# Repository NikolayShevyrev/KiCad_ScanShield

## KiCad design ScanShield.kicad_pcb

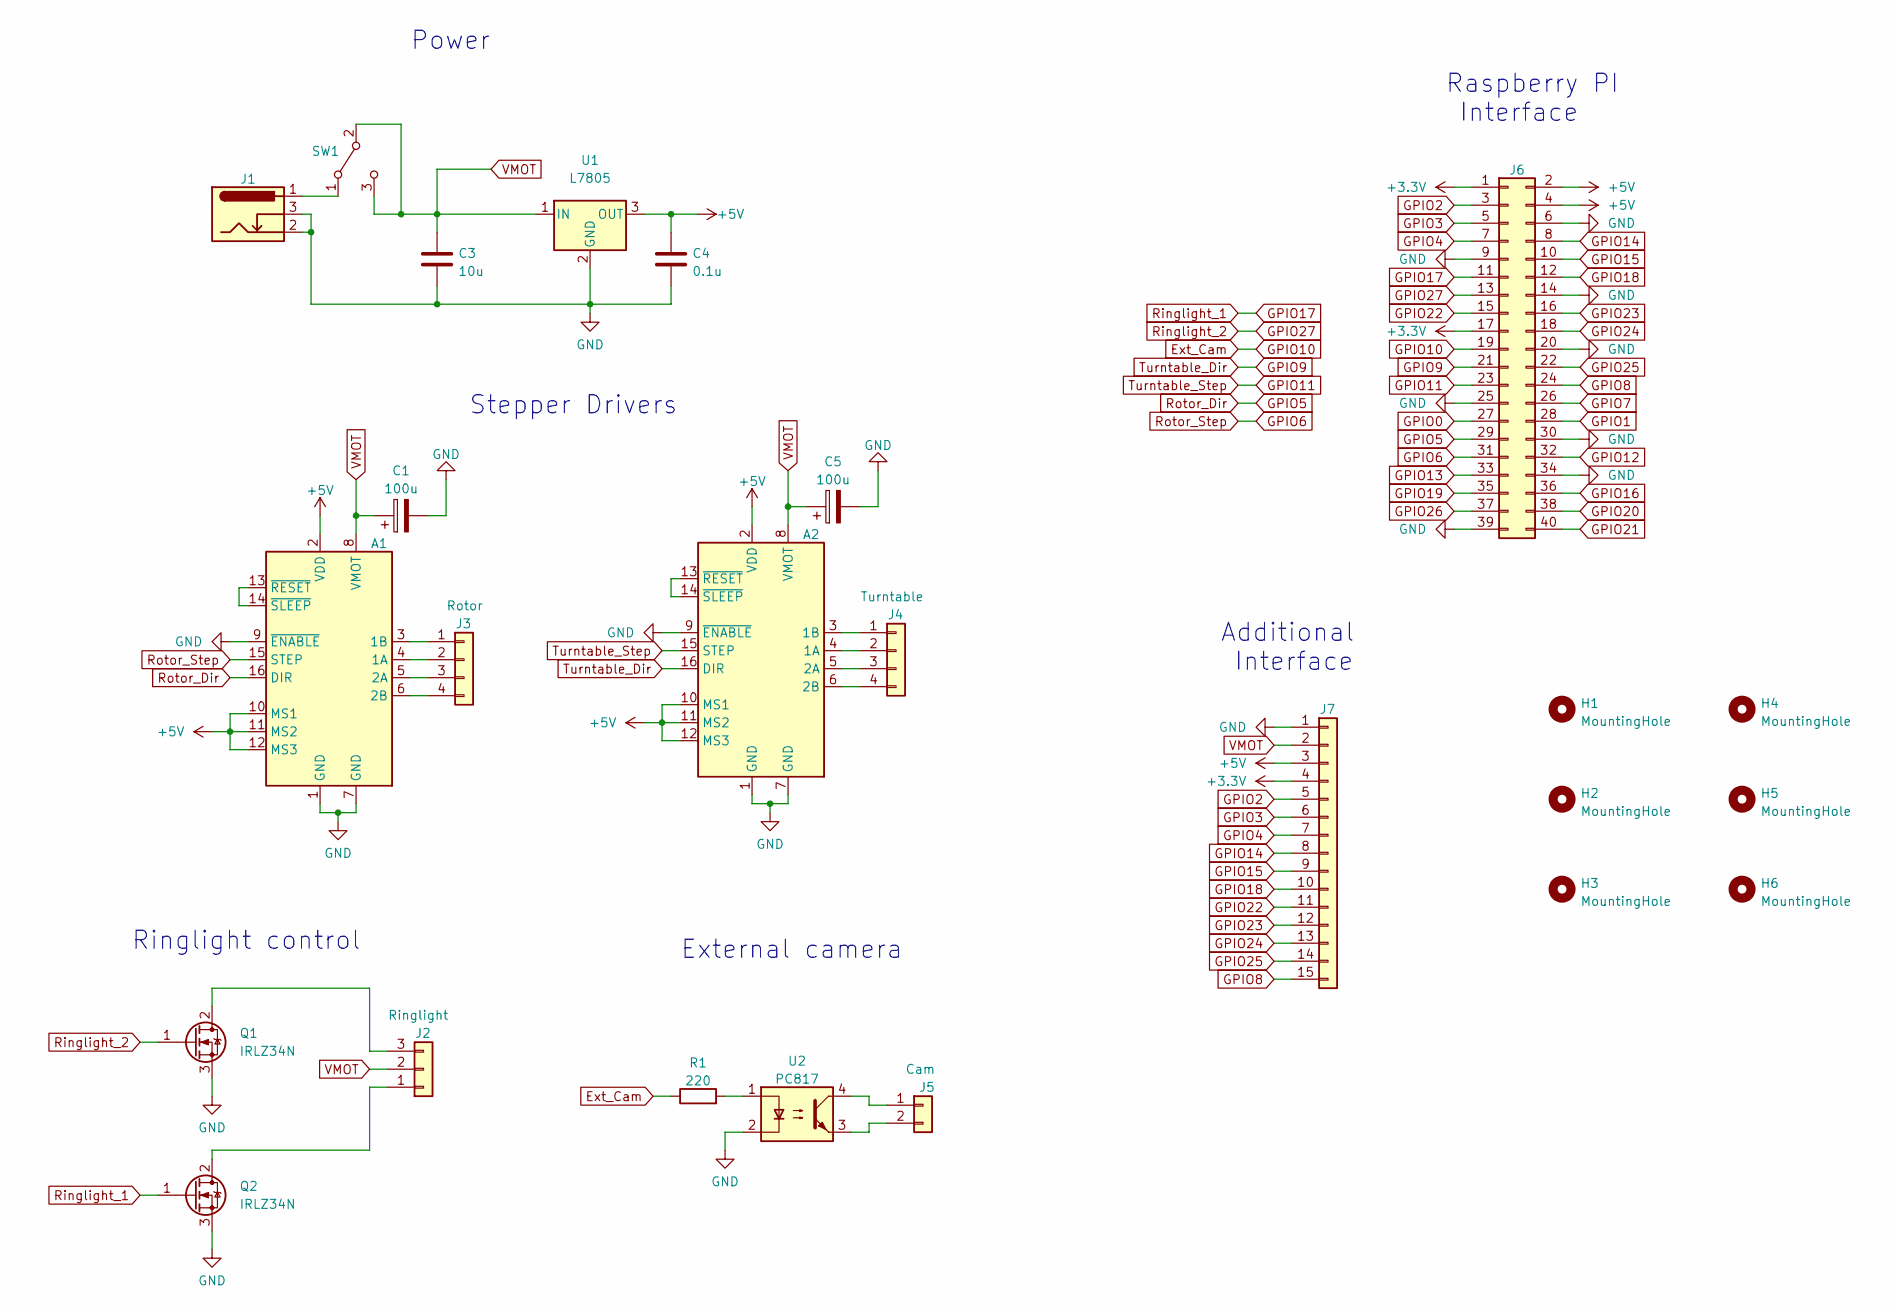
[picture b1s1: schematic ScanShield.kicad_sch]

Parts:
A1, A2: Pololu_Breakout_A4988; Pololu_Breakout-16_15.2x20.3mm
C1, C5: 100u; CP_Radial_D6.3mm_P2.50mm
C3: 10u; C_0805_2012Metric_Pad1.18x1.45mm_HandSolder
C4: 0.1u; C_0805_2012Metric_Pad1.18x1.45mm_HandSolder
H1, H2, H3, H4, H5, H6: MountingHole; MountingHole_3.5mm
J1: Barrel_Jack_Switch_Pin3Ring; BarrelJack_Kycon_KLDX-0202-xC_Horizontal
J2: Ringlight; JST_XH_S3B-XH-A_1x03_P2.50mm_Horizontal
J3: Rotor; PinHeader_1x04_P2.54mm_Vertical
J4: Turntable; PinHeader_1x04_P2.54mm_Vertical
J5: Cam; PinSocket_1x02_P2.54mm_Vertical
J6: Conn_02x20_Odd_Even; PinSocket_2x20_P2.54mm_Vertical
J7: Conn_01x15; PinHeader_1x15_P2.54mm_Vertical
Q1, Q2: IRLZ34N; TO-220-3_Vertical
R1: 220; R_Axial_DIN0207_L6.3mm_D2.5mm_P10.16mm_Horizontal
SW1: SW_SPDT; 1101M2S3CQE2
U1: L7805; PinHeader_1x03_P2.54mm_Vertical
U2: PC817; DIP-4_W7.62mm

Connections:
+3.3V: J6.1, J6.17, J7.4
+5V: A1.2 (VDD), A1.10 (MS1), A1.11 (MS2), A1.12 (MS3), A2.2 (VDD), A2.10 (MS1), A2.11 (MS2), A2.12 (MS3), C4.1, J6.2, J6.4, J7.3, U1.3 (OUT)
Ext_Cam: J6.19, R1.1
GND: A1.1 (GND), A1.7 (GND), A1.9 (~ENABLE), A2.1 (GND), A2.7 (GND), A2.9 (~ENABLE), C1.2, C3.2, C4.2, C5.2, J1.2, J1.3, J6.6, J6.9, J6.14, J6.20, J6.25, J6.30, J6.34, J6.39, J7.1, Q1.3 (S), Q2.3 (S), U1.2 (GND), U2.2
GPIO0: J6.27
GPIO1: J6.28
GPIO2: J6.3, J7.5
GPIO3: J6.5, J7.6
GPIO4: J6.7, J7.7
GPIO5: A1.16 (DIR), J6.29
GPIO6: A1.15 (STEP), J6.31
GPIO7: J6.26
GPIO8: J6.24, J7.15
GPIO9: A2.16 (DIR), J6.21
GPIO11: A2.15 (STEP), J6.23
GPIO12: J6.32
GPIO13: J6.33
GPIO14: J6.8, J7.8
GPIO15: J6.10, J7.9
GPIO16: J6.36
GPIO17: J6.11, Q2.1 (G)
GPIO18: J6.12, J7.10
GPIO19: J6.35
GPIO20: J6.38
GPIO21: J6.40
GPIO22: J6.15, J7.11
GPIO23: J6.16, J7.12
GPIO24: J6.18, J7.13
GPIO25: J6.22, J7.14
GPIO26: J6.37
GPIO27: J6.13, Q1.1 (G)
unnamed: A1.3 (1B), J3.1
unnamed: A1.4 (1A), J3.2
unnamed: A1.5 (2A), J3.3
unnamed: A1.6 (2B), J3.4
unnamed: A1.13 (~RESET), A1.14 (~SLEEP)
unnamed: A2.3 (1B), J4.1
unnamed: A2.4 (1A), J4.2
unnamed: A2.5 (2A), J4.3
unnamed: A2.6 (2B), J4.4
unnamed: A2.13 (~RESET), A2.14 (~SLEEP)
unnamed: J1.1, SW1.1 (A)
unnamed: J2.1, Q2.2 (D)
unnamed: J2.3, Q1.2 (D)
unnamed: J5.1, U2.4
unnamed: J5.2, U2.3
unnamed: R1.2, U2.1
VMOT: A1.8 (VMOT), A2.8 (VMOT), C1.1, C3.1, C5.1, J2.2, J7.2, SW1.2 (B), SW1.3 (C), U1.1 (IN)

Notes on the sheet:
Additional Interface
Power
Stepper Drivers
External camera
Raspberry PI Interface
Ringlight control

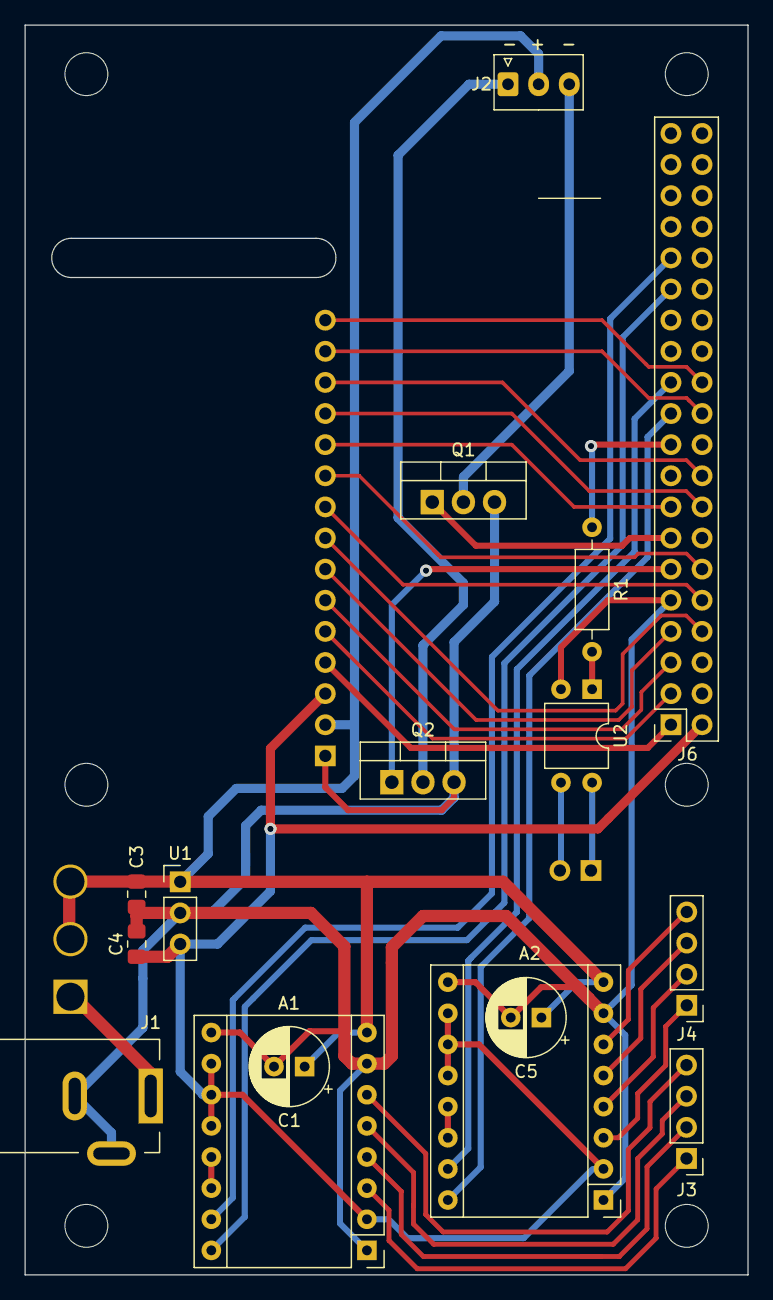
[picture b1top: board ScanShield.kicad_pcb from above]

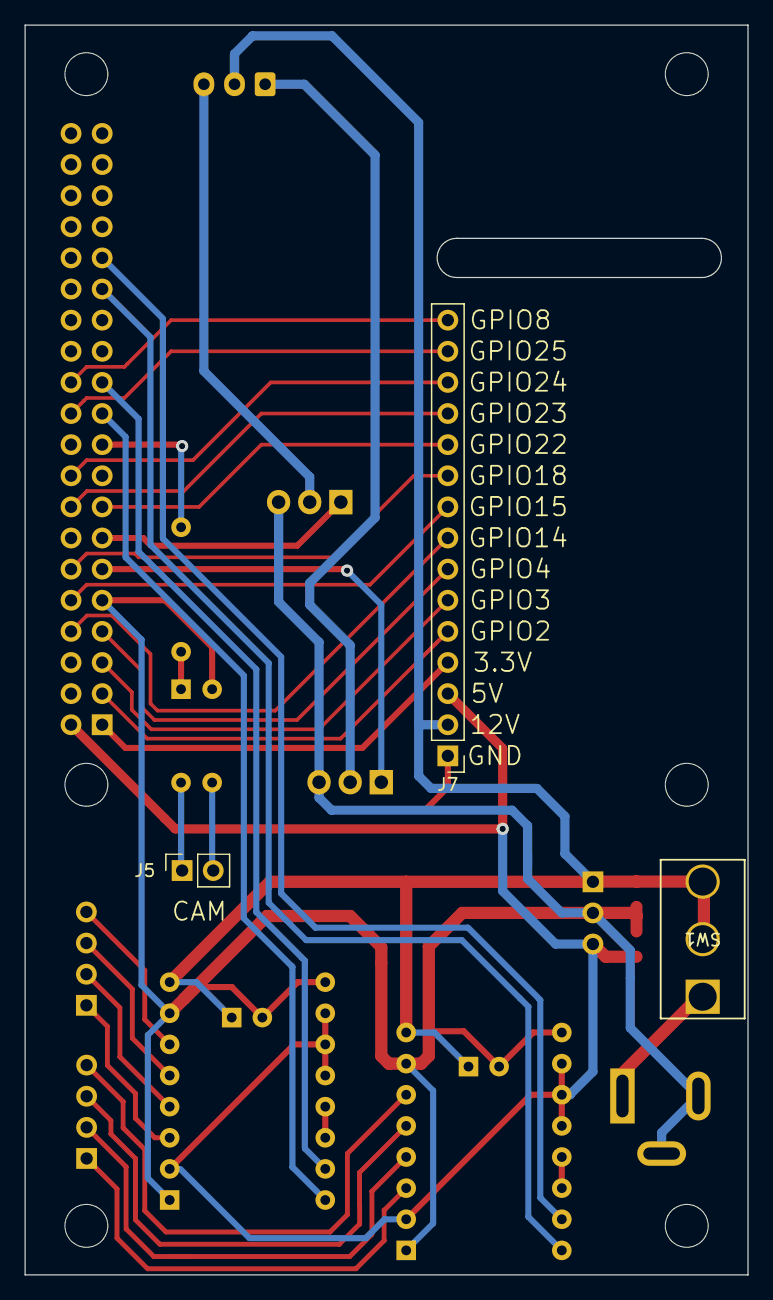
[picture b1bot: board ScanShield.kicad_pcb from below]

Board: 2 copper layers, 59.0 x 102.0 mm, 25 parts (3 on the bottom side), 38 nets.

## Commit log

2024-03-15 Added mounting holes and board outline
2024-04-07 Modified pcb, first variant
2024-04-12 Changed board cutout
2024-04-16 Second pcb draft
